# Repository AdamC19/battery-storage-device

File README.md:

# Battery Storage Device
Hardware files for a device that will storage charge batteries

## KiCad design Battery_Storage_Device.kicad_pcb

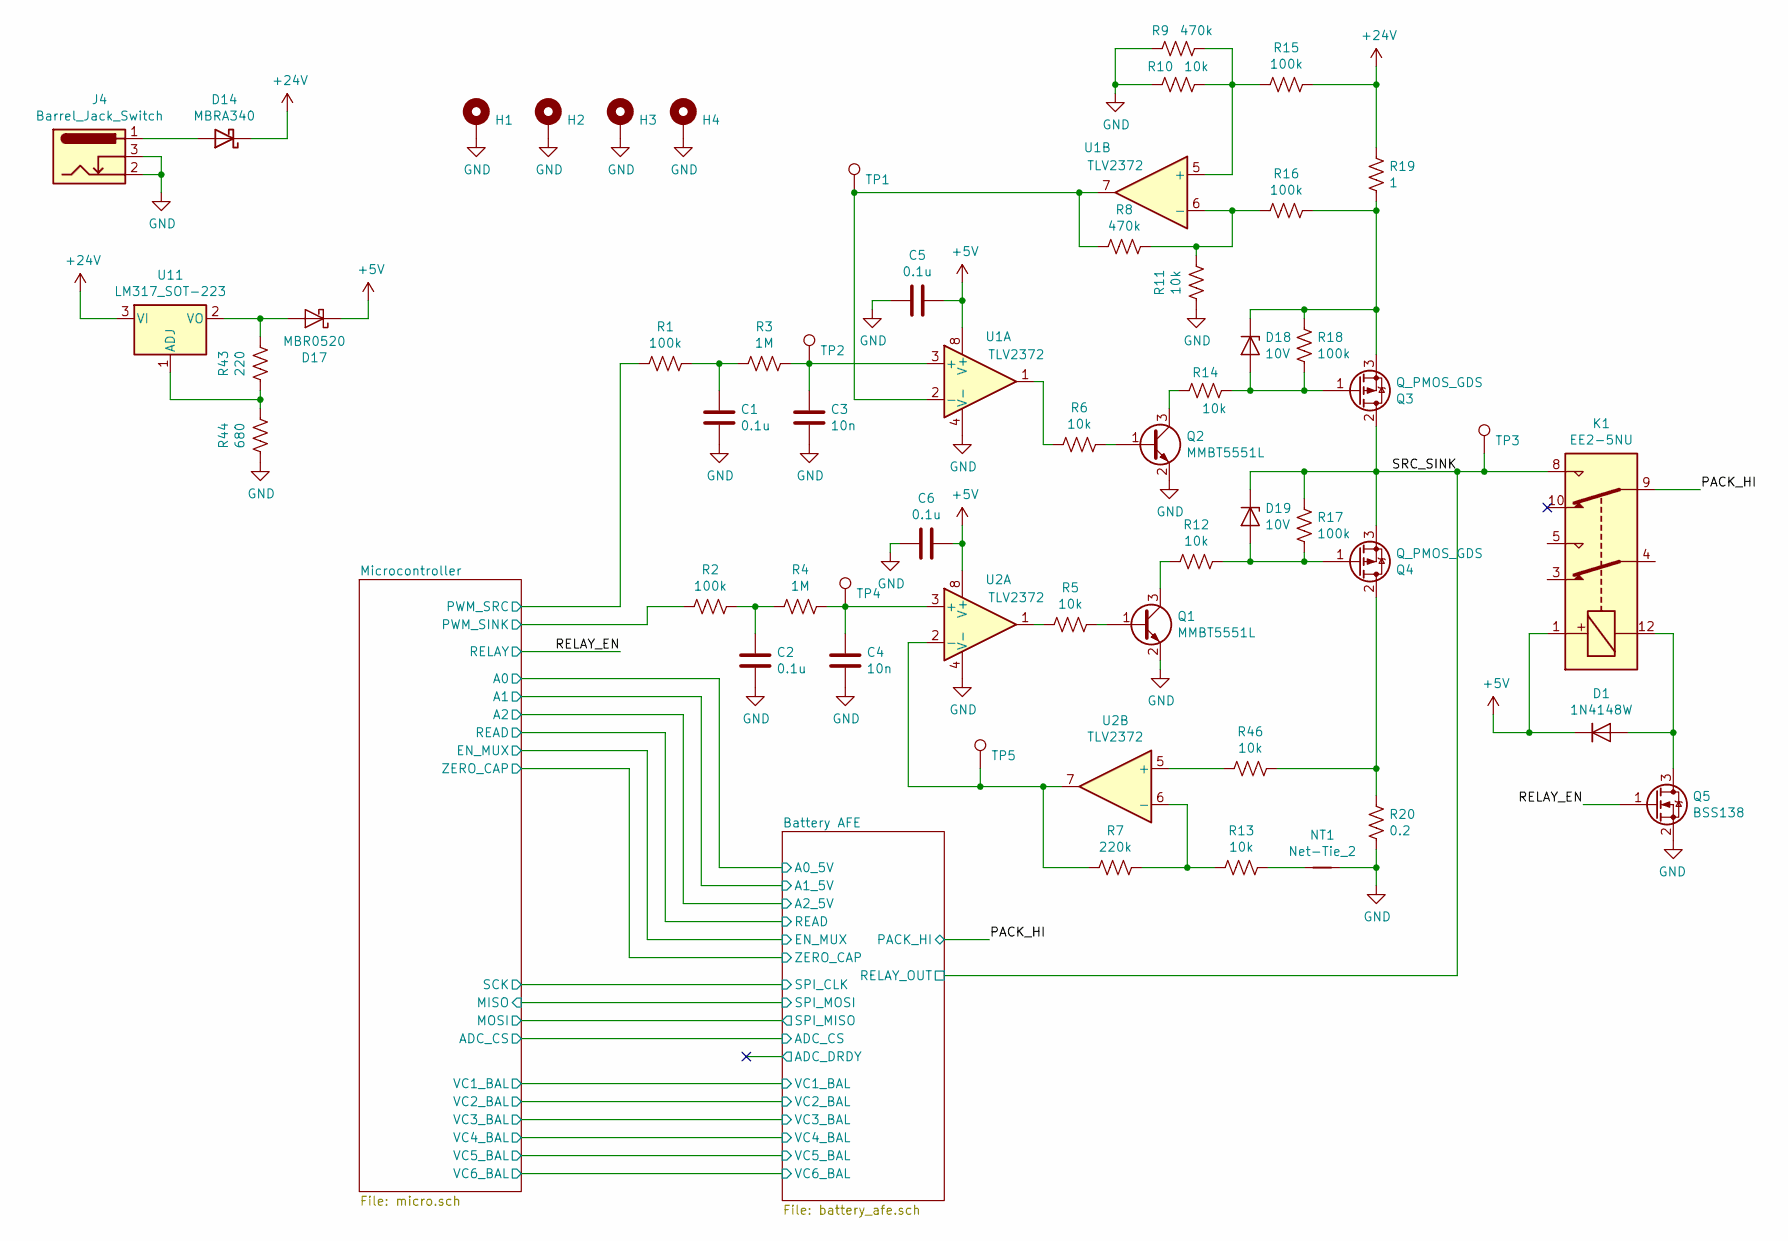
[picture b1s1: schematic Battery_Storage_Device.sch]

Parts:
C1, C2, C5, C6: 0.1u; C_0805_2012Metric
C3, C4: 10n; C_0805_2012Metric
D1: 1N4148W; D_SOD-123
D14: MBRA340; D_SMA
D17: MBR0520; D_SOD-123
D18, D19: 10V; D_SOD-123
H1, H2, H3, H4: MountingHole_Pad; MountingHole_2.7mm_M2.5_Pad
J4: Barrel_Jack_Switch; BarrelJack_Wuerth_6941xx301002
K1: EE2-5NU; Relay_DPDT_Kemet_EE2_NU
NT1: Net-Tie_2; NetTie-2_SMD_Pad0.5mm
Q1, Q2: MMBT5551L; SOT-23
Q3, Q4: Q_PMOS_GDS; TO-263-2
Q5: BSS138; SOT-23
R1, R2, R15, R16, R17, R18: 100k; R_0805_2012Metric
R3, R4: 1M; R_0805_2012Metric
R5, R6, R10, R11, R12, R13, R14, R46: 10k; R_0805_2012Metric
R7: 220k; R_0805_2012Metric
R8, R9: 470k; R_0805_2012Metric
R19: 1; R_1206_3216Metric
R20: 0.2; R_1206_3216Metric
R43: 220; R_0805_2012Metric
R44: 680; R_0805_2012Metric
TP1, TP2, TP3, TP4, TP5: TestPoint; TestPoint_THTPad_D2.0mm_Drill1.0mm
U1, U2: TLV2372; SOIC-8_3.9x4.9mm_P1.27mm
U11: LM317_SOT-223; SOT-223-3_TabPin2

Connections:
+5V: C5.2, C6.2, D1.1 (K), D17.1 (K), K1.1, U1.8 (V+), U2.8 (V+); also elsewhere on the board
+24V: D14.1 (K), R15.2, R19.1, U11.3 (VI); also elsewhere on the board
/Microcontroller/PWM_SINK: R2.1; also elsewhere on the board
/Microcontroller/PWM_SRC: R1.1; also elsewhere on the board
/PACK_HI: K1.9; also elsewhere on the board
/RELAY_EN: Q5.1 (G); also elsewhere on the board
/SRC_SINK: D19.1 (K), K1.8, Q3.2 (D), Q4.3 (S), R17.1, TP3.1; also elsewhere on the board
GND: C1.2, C2.2, C3.2, C4.2, C5.1, C6.1, H1.1, H2.1, H3.1, H4.1, J4.2, J4.3, NT1.2, Q1.2 (E), Q2.2 (E), Q5.2 (S), R9.1, R10.1, R11.1, R20.2, R44.1, U1.4 (V-), U2.4 (V-); also elsewhere on the board
unnamed: C1.1, R1.2, R3.1
unnamed: C2.1, R2.2, R4.1
unnamed: C3.1, R3.2, TP2.1, U1.3 (+)
unnamed: C4.1, R4.2, TP4.1, U2.3 (+)
unnamed: D1.2 (A), K1.12, Q5.3 (D)
unnamed: D14.2 (A), J4.1
unnamed: D17.2 (A), R43.2, U11.2 (VO)
unnamed: D18.1 (K), Q3.3 (S), R16.2, R18.1, R19.2
unnamed: D18.2 (A), Q3.1 (G), R14.2, R18.2
unnamed: D19.2 (A), Q4.1 (G), R12.2, R17.2
unnamed: NT1.1, R13.1
unnamed: Q1.1 (B), R5.2
unnamed: Q1.3 (C), R12.1
unnamed: Q2.1 (B), R6.2
unnamed: Q2.3 (C), R14.1
unnamed: Q4.2 (D), R20.1, R46.1
unnamed: R5.1, U2.1
unnamed: R6.1, U1.1
unnamed: R7.2, TP5.1, U2.2 (-), U2.7
unnamed: R8.1, TP1.1, U1.2 (-), U1.7
unnamed: R9.2, R10.2, R15.1, U1.5 (+)
unnamed: R8.2, R11.2, R16.1, U1.6 (-)
unnamed: R7.1, R13.2, U2.6 (-)
unnamed: R43.1, R44.2, U11.1 (ADJ)
unnamed: R46.2, U2.5 (+)

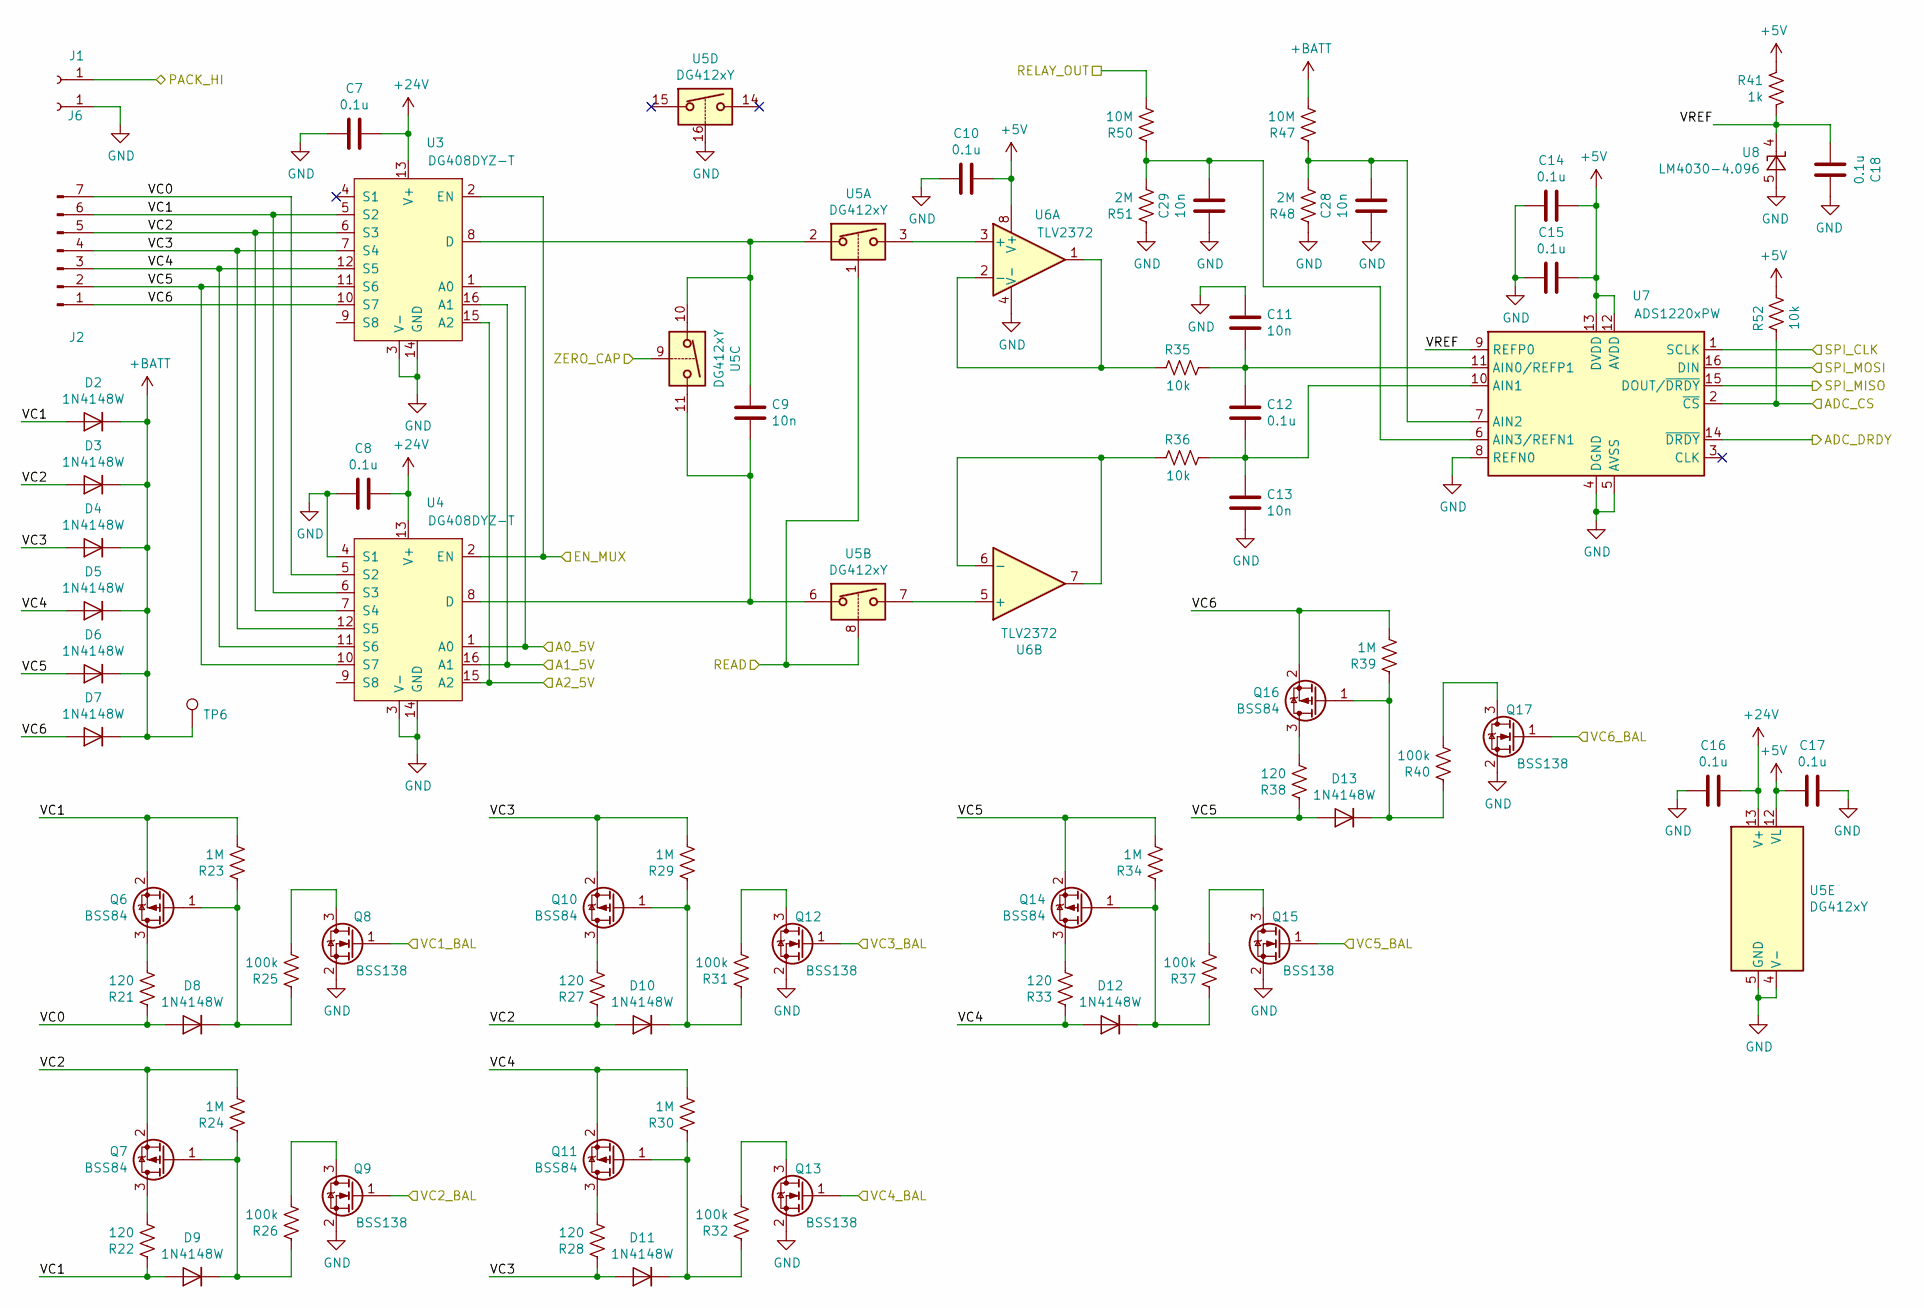
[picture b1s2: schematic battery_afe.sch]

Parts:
C7, C8, C10, C12, C14, C15, C16, C17, C18: 0.1u; C_0805_2012Metric
C9, C11, C13, C28, C29: 10n; C_0805_2012Metric
D2, D3, D4, D5, D6, D7, D8, D9, D10, D11, D12, D13: 1N4148W; D_SOD-123
J1, J6: Conn_01x01_Female; banana_jack_right_angle
J2: Conn_01x07_Male; PinHeader_1x07_P2.54mm_Horizontal
Q6, Q7, Q10, Q11, Q14, Q16: BSS84; SOT-23
Q8, Q9, Q12, Q13, Q15, Q17: BSS138; SOT-23
R21, R22, R27, R28, R33, R38: 120; R_0805_2012Metric
R23, R24, R29, R30, R34, R39: 1M; R_0805_2012Metric
R25, R26, R31, R32, R37, R40: 100k; R_0805_2012Metric
R35, R36, R52: 10k; R_0805_2012Metric
R41: 1k; R_0805_2012Metric
R47, R50: 10M; R_0805_2012Metric
R48, R51: 2M; R_0805_2012Metric
TP6: TestPoint; TestPoint_THTPad_D2.0mm_Drill1.0mm
U3, U4: DG408DYZ-T; SOIC-16_3.9x9.9mm_P1.27mm
U5: DG412xY; SOIC-16_3.9x9.9mm_P1.27mm
U6: TLV2372; SOIC-8_3.9x4.9mm_P1.27mm
U7: ADS1220xPW; TSSOP-16_4.4x5mm_P0.65mm
U8: LM4030-4.096; SOT-23-5

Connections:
+5V: C10.2, C14.1, C15.1, C17.1, R41.1, R52.2, U5.12 (VL), U6.8 (V+), U7.12 (AVDD), U7.13 (DVDD); also elsewhere on the board
+24V: C7.1, C8.1, C16.1, U3.13 (V+), U4.13 (V+), U5.13 (V+); also elsewhere on the board
+BATT: D2.1 (K), D3.1 (K), D4.1 (K), D5.1 (K), D6.1 (K), D7.1 (K), R47.2, TP6.1
/Battery AFE/ADC_CS: R52.1, U7.2 (~CS); also elsewhere on the board
/Battery AFE/ADC_DRDY: U7.14 (~DRDY)
/Battery AFE/EN_MUX: U3.2 (EN), U4.2 (EN); also elsewhere on the board
/Battery AFE/READ: U5.1, U5.8; also elsewhere on the board
/Battery AFE/VC0: D8.2 (A), J2.7, R21.1, U4.5 (S2)
/Battery AFE/VC1: D2.2 (A), D9.2 (A), J2.6, Q6.2 (S), R22.1, R23.2, U3.5 (S2), U4.6 (S3)
/Battery AFE/VC1_BAL: Q8.1 (G); also elsewhere on the board
/Battery AFE/VC2: D3.2 (A), D10.2 (A), J2.5, Q7.2 (S), R24.2, R27.1, U3.6 (S3), U4.7 (S4)
/Battery AFE/VC2_BAL: Q9.1 (G); also elsewhere on the board
/Battery AFE/VC3: D4.2 (A), D11.2 (A), J2.4, Q10.2 (S), R28.1, R29.2, U3.7 (S4), U4.12 (S5)
/Battery AFE/VC3_BAL: Q12.1 (G); also elsewhere on the board
/Battery AFE/VC4: D5.2 (A), D12.2 (A), J2.3, Q11.2 (S), R30.2, R33.1, U3.12 (S5), U4.11 (S6)
/Battery AFE/VC4_BAL: Q13.1 (G); also elsewhere on the board
/Battery AFE/VC5: D6.2 (A), D13.2 (A), J2.2, Q14.2 (S), R34.2, R38.1, U3.11 (S6), U4.10 (S7)
/Battery AFE/VC5_BAL: Q15.1 (G); also elsewhere on the board
/Battery AFE/VC6: D7.2 (A), J2.1, Q16.2 (S), R39.2, U3.10 (S7)
/Battery AFE/VC6_BAL: Q17.1 (G); also elsewhere on the board
/Battery AFE/VREF: C18.1, R41.2, U7.9 (REFP0), U8.4 (K)
/Battery AFE/ZERO_CAP: U5.9; also elsewhere on the board
/Microcontroller/A0: U3.1 (A0), U4.1 (A0); also elsewhere on the board
/Microcontroller/A1: U3.16 (A1), U4.16 (A1); also elsewhere on the board
/Microcontroller/A2: U3.15 (A2), U4.15 (A2); also elsewhere on the board
/Microcontroller/MISO: U7.16 (DIN); also elsewhere on the board
/Microcontroller/MOSI: U7.15 (DOUT/~DRDY); also elsewhere on the board
/Microcontroller/SCK: U7.1 (SCLK); also elsewhere on the board
/PACK_HI: J1.1; also elsewhere on the board
/SRC_SINK: R50.2; also elsewhere on the board
GND: C7.2, C8.2, C10.1, C11.1, C13.2, C14.2, C15.2, C16.2, C17.2, C18.2, C28.2, C29.2, J6.1, Q8.2 (S), Q9.2 (S), Q12.2 (S), Q13.2 (S), Q15.2 (S), Q17.2 (S), R48.1, R51.1, U3.3 (V-), U3.14 (GND), U4.3 (V-), U4.4 (S1), U4.14 (GND), U5.4 (V-), U5.5 (GND), U5.16, U6.4 (V-), U7.4 (DGND), U7.5 (AVSS), U7.8 (REFN0), U8.5 (A); also elsewhere on the board
unnamed: C9.1, U3.8 (D), U5.2, U5.10
unnamed: C9.2, U4.8 (D), U5.6, U5.11
unnamed: C11.2, C12.1, R35.2, U7.11 (AIN0/REFP1)
unnamed: C12.2, C13.1, R36.2, U7.10 (AIN1)
unnamed: C28.1, R47.1, R48.2, U7.7 (AIN2)
unnamed: C29.1, R50.1, R51.2, U7.6 (AIN3/REFN1)
unnamed: D8.1 (K), Q6.1 (G), R23.1, R25.1
unnamed: D9.1 (K), Q7.1 (G), R24.1, R26.1
unnamed: D10.1 (K), Q10.1 (G), R29.1, R31.1
unnamed: D11.1 (K), Q11.1 (G), R30.1, R32.1
unnamed: D12.1 (K), Q14.1 (G), R34.1, R37.1
unnamed: D13.1 (K), Q16.1 (G), R39.1, R40.1
unnamed: Q6.3 (D), R21.2
unnamed: Q7.3 (D), R22.2
unnamed: Q8.3 (D), R25.2
unnamed: Q9.3 (D), R26.2
unnamed: Q10.3 (D), R27.2
unnamed: Q11.3 (D), R28.2
unnamed: Q12.3 (D), R31.2
unnamed: Q13.3 (D), R32.2
unnamed: Q14.3 (D), R33.2
unnamed: Q15.3 (D), R37.2
unnamed: Q16.3 (D), R38.2
unnamed: Q17.3 (D), R40.2
unnamed: R35.1, U6.1, U6.2 (-)
unnamed: R36.1, U6.6 (-), U6.7
unnamed: U5.3, U6.3 (+)
unnamed: U5.7, U6.5 (+)

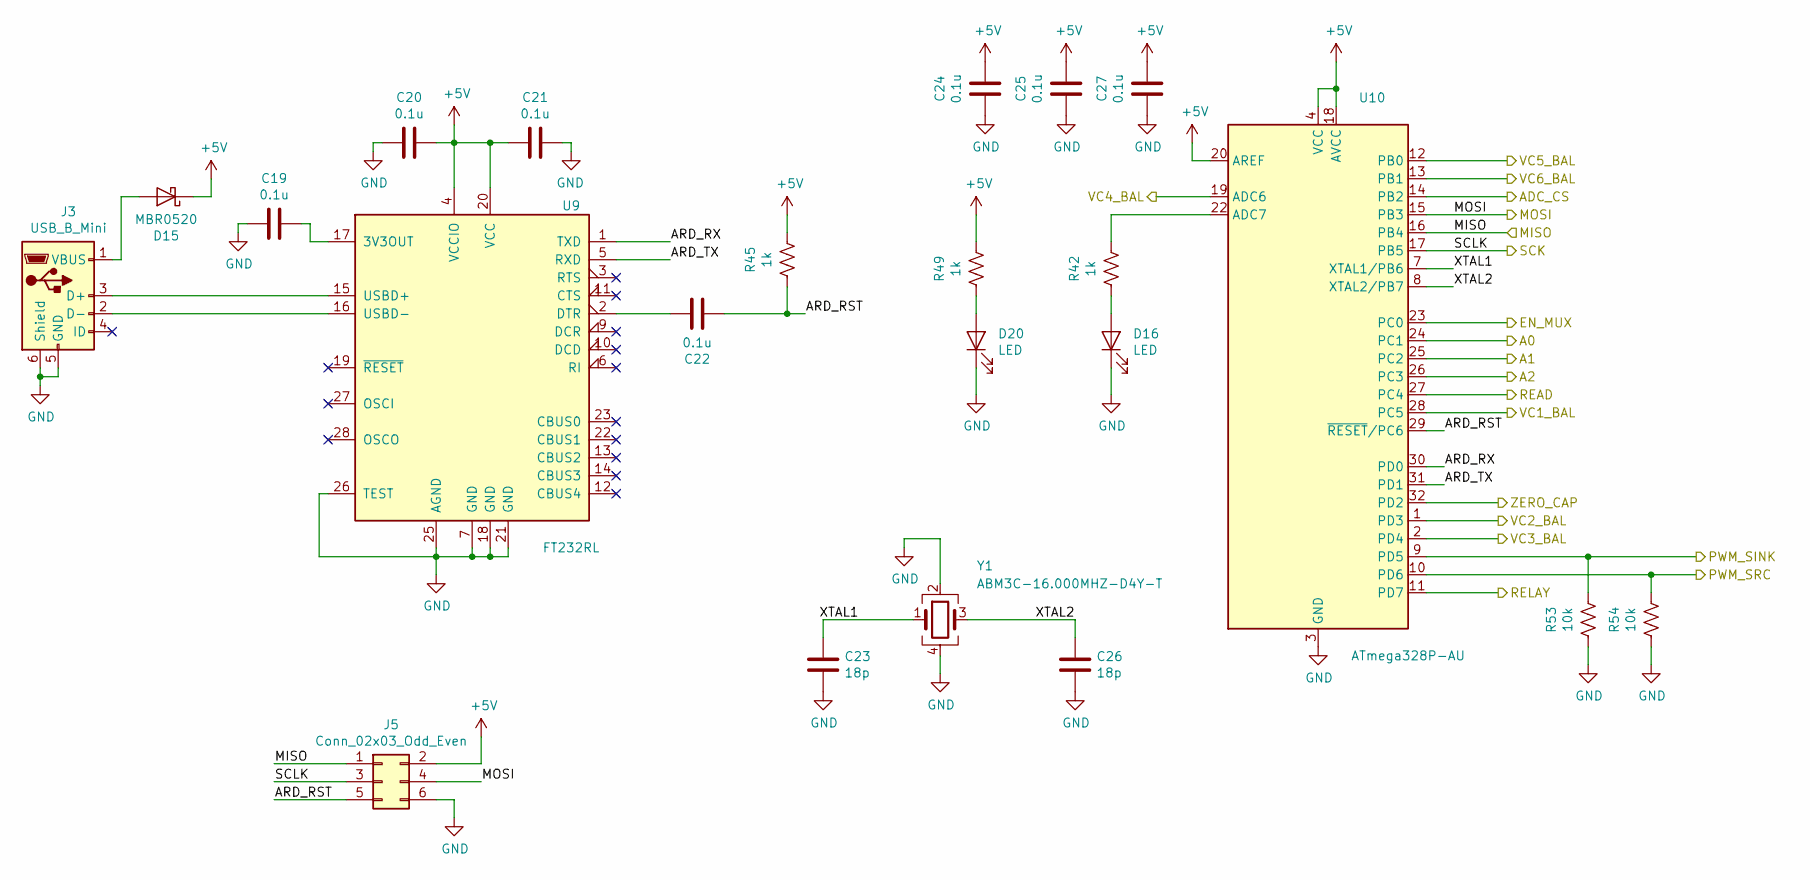
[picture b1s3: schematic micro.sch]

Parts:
C19, C20, C21, C22, C24, C25, C27: 0.1u; C_0805_2012Metric
C23, C26: 18p; C_0603_1608Metric
D15: MBR0520; D_SOD-123
D16, D20: LED; LED_0805_2012Metric
J3: USB_B_Mini; USB_Mini-B_Wuerth_65100516121_Horizontal
J5: Conn_02x03_Odd_Even; PinHeader_2x03_P2.54mm_Vertical
R42, R45, R49: 1k; R_0805_2012Metric
R53, R54: 10k; R_0805_2012Metric
U9: FT232RL; SSOP-28_5.3x10.2mm_P0.65mm
U10: ATmega328P-AU; TQFP-32_7x7mm_P0.8mm
Y1: ABM3C-16.000MHZ-D4Y-T; Crystal_SMD_Abracon_ABM3C-4Pin_5.0x3.2mm

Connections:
+5V: C20.2, C21.2, C24.2, C25.2, C27.2, D15.1 (K), J5.2, R45.2, R49.2, U9.4 (VCCIO), U9.20 (VCC), U10.4 (VCC), U10.6 (VCC), U10.18 (AVCC), U10.20 (AREF); also elsewhere on the board
/Battery AFE/ADC_CS: U10.14 (PB2); also elsewhere on the board
/Battery AFE/EN_MUX: U10.23 (PC0); also elsewhere on the board
/Battery AFE/READ: U10.27 (PC4); also elsewhere on the board
/Battery AFE/VC1_BAL: U10.28 (PC5); also elsewhere on the board
/Battery AFE/VC2_BAL: U10.1 (PD3); also elsewhere on the board
/Battery AFE/VC3_BAL: U10.2 (PD4); also elsewhere on the board
/Battery AFE/VC4_BAL: U10.19 (ADC6); also elsewhere on the board
/Battery AFE/VC5_BAL: U10.12 (PB0); also elsewhere on the board
/Battery AFE/VC6_BAL: U10.13 (PB1); also elsewhere on the board
/Battery AFE/ZERO_CAP: U10.32 (PD2); also elsewhere on the board
/Microcontroller/A0: U10.24 (PC1); also elsewhere on the board
/Microcontroller/A1: U10.25 (PC2); also elsewhere on the board
/Microcontroller/A2: U10.26 (PC3); also elsewhere on the board
/Microcontroller/ARD_RST: C22.1, J5.5, R45.1, U10.29 (~RESET~/PC6)
/Microcontroller/ARD_RX: U9.1 (TXD), U10.30 (PD0)
/Microcontroller/ARD_TX: U9.5 (RXD), U10.31 (PD1)
/Microcontroller/MISO: J5.1, U10.16 (PB4); also elsewhere on the board
/Microcontroller/MOSI: J5.4, U10.15 (PB3); also elsewhere on the board
/Microcontroller/PWM_SINK: R53.2, U10.9 (PD5); also elsewhere on the board
/Microcontroller/PWM_SRC: R54.2, U10.10 (PD6); also elsewhere on the board
/Microcontroller/SCK: J5.3, U10.17 (PB5); also elsewhere on the board
/Microcontroller/XTAL1: C23.1, U10.7 (XTAL1/PB6), Y1.1
/Microcontroller/XTAL2: C26.1, U10.8 (XTAL2/PB7), Y1.3
/RELAY_EN: U10.11 (PD7); also elsewhere on the board
GND: C19.1, C20.1, C21.1, C23.2, C24.1, C25.1, C26.2, C27.1, D16.1 (K), D20.1 (K), J3.5 (GND), J3.6 (Shield), J5.6, R53.1, R54.1, U9.7 (GND), U9.18 (GND), U9.21 (GND), U9.25 (AGND), U9.26 (TEST), U10.3 (GND), U10.5 (GND), U10.21 (GND), Y1.2, Y1.4; also elsewhere on the board
unnamed: C19.2, U9.17 (3V3OUT)
unnamed: C22.2, U9.2 (DTR)
unnamed: D15.2 (A), J3.1 (VBUS)
unnamed: D16.2 (A), R42.1
unnamed: D20.2 (A), R49.1
unnamed: J3.2 (D-), U9.16 (USBD-)
unnamed: J3.3 (D+), U9.15 (USBD+)
unnamed: R42.2, U10.22 (ADC7)

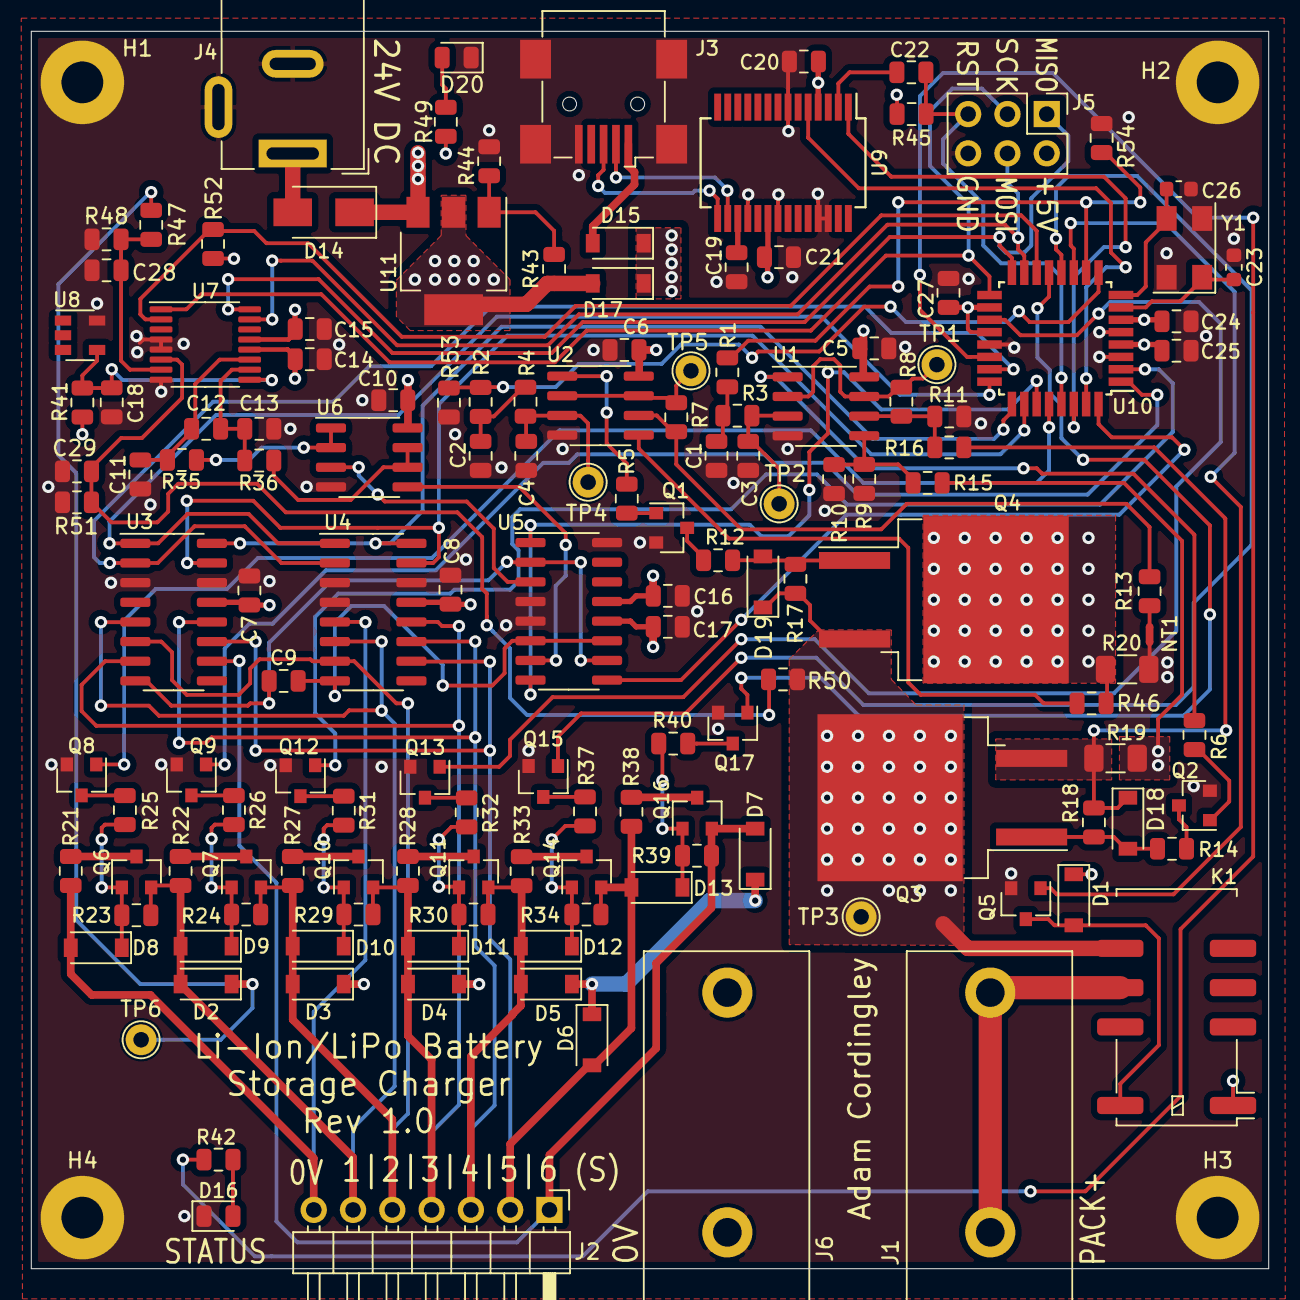
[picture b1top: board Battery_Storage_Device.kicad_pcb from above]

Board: 4 copper layers, 80.0 x 80.0 mm, 150 parts (0 on the bottom side), 99 nets.

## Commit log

2020-09-26 Add empty KiCad files
2020-09-29 Initial work complete
2020-09-29 Updates to the AFE power scheme to prevent discharging of the batteries
2020-11-16 New power banana jacks, general updates
2020-11-18 Final PCB and gerbers
2020-11-26 Specify exact pin header part number
